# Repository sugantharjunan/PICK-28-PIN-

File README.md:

# PIC 28-Pin Development Board – KiCad PCB Design

A compact and versatile **PIC 28-Pin Development Board** designed using **KiCad EDA** for schematic capture and PCB layout. This project is based on the **PIC16F873A / PIC16F876A / PIC16F877A family architecture**, providing GPIO breakout pins, push buttons, EEPROM interface, IR sensor support, LEDs, and expansion headers for embedded systems development.

The board is suitable for learning PIC microcontrollers, embedded programming, sensor interfacing, and electronics prototyping.

---

# Project Overview

This project demonstrates:

* PIC 28-pin microcontroller minimum system design
* PCB layout using KiCad
* EEPROM interfacing
* IR sensor interface
* Push-button inputs
* LED status indicators
* GPIO breakout headers
* 3D PCB visualization

---

# Features

* Supports 28-pin PIC microcontroller
* GPIO breakout headers
* Push-button interface
* External EEPROM support
* IR sensor module interface
* Status LEDs
* Compact PCB layout
* Through-hole component design
* Designed using KiCad

---

# Software Used

* KiCad

Official Website: [KiCad Official Website](https://www.kicad.org?utm_source=chatgpt.com)

---

# Hardware Components

| Component               | Description                  |
| ----------------------- | ---------------------------- |
| PIC16F873A / PIC16F876A | PIC Microcontroller          |
| AT24Cxx                 | EEPROM Memory IC             |
| TSOP1738                | IR Receiver Module           |
| Push Buttons            | User Input                   |
| LEDs                    | Status Indicators            |
| Capacitors              | Power filtering              |
| Resistors               | Pull-up and current limiting |
| Pin Headers             | GPIO breakout                |

---

# Project Structure

```bash id="f4jv7a"
PIC-28PIN-DEVELOPMENT-BOARD/
│
├── Schematic/
│   └── pic_28pin_board.kicad_sch
│
├── PCB/
│   └── pic_28pin_board.kicad_pcb
│
├── Gerber/
│   └── Manufacturing_Files
│
├── Images/
│   ├── PIC_28PIN_3D_FRONT.png
│   ├── PIC_28PIN_3D_BACK.png
│   ├── PIC_28PIN_PCB.png
│   └── PIC_28PIN_SCHEMATIC.png
│
└── README.md
```

---

# Circuit Description

The development board is centered around a **28-pin PIC microcontroller** with additional peripheral support circuits.

The design includes:

* Push-button input interface
* EEPROM communication support
* IR receiver module connection
* LED output indicators
* GPIO expansion headers
* Power regulation and filtering

---

# Working Principle

1. +5V supply powers the microcontroller and peripherals.
2. PIC microcontroller executes embedded firmware.
3. Push buttons provide user input.
4. EEPROM stores external data.
5. IR receiver detects remote control signals.
6. LEDs indicate system status or outputs.
7. GPIO headers allow external module interfacing.

---

# PCB Design

The PCB was designed with:

* Organized GPIO routing
* Compact component placement
* Easy soldering access
* Through-hole assembly
* Proper grounding layout
* Beginner-friendly prototyping structure

---

# Electrical Specifications

| Parameter         | Value             |
| ----------------- | ----------------- |
| Microcontroller   | PIC 28-Pin Series |
| Supply Voltage    | +5V DC            |
| EEPROM Support    | Yes               |
| IR Sensor Support | Yes               |
| GPIO Expansion    | Yes               |
| PCB Tool          | KiCad             |

---

# Pin Interfaces

The board exposes:

* Digital GPIO Pins
* Analog Input Pins
* UART Communication
* I2C Interface
* SPI Interface
* EEPROM Interface
* IR Sensor Interface

for embedded application development.

---

# Applications

* Embedded Systems Development
* PIC Programming Practice
* Sensor Interfacing
* IR Remote Projects
* EEPROM Data Logging
* Robotics
* Automation Projects
* Academic Embedded Labs

---

# Development Notes

Compatible with:

* MPLAB X IDE
* XC8 Compiler
* PICkit Programmer
* MikroC
* Embedded C Programming

---

# Future Improvements

* Add onboard USB programmer
* Add voltage regulator section
* Add LCD display connector
* Add relay driver outputs
* Add wireless communication modules

---

This project is open-source and available under the MIT License.

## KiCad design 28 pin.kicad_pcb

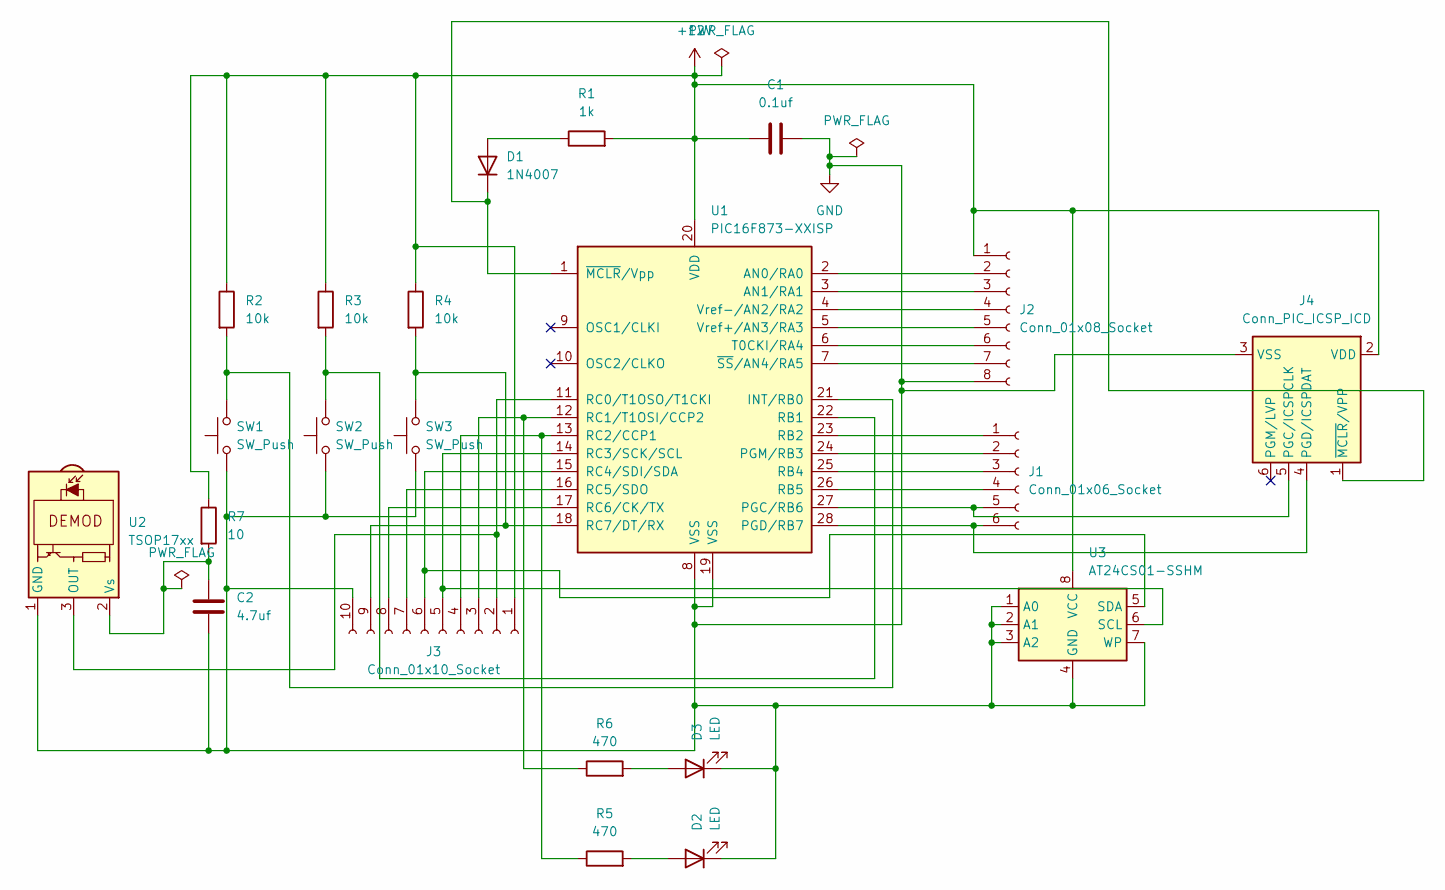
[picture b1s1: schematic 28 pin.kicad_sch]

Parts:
C1: 0.1uf; CP_Radial_D4.0mm_P1.50mm
C2: 4.7uf; CP_Radial_D4.0mm_P1.50mm
D1: 1N4007; D_DO-41_SOD81_P10.16mm_Horizontal
D2, D3: LED; LED_D3.0mm
J1: Conn_01x06_Socket; PinSocket_1x06_P1.27mm_Vertical
J2: Conn_01x08_Socket; PinSocket_1x08_P1.27mm_Vertical
J3: Conn_01x10_Socket; PinSocket_1x10_P1.27mm_Vertical
J4: Conn_PIC_ICSP_ICD; PinSocket_1x06_P2.54mm_Horizontal
R1: 1k; R_Axial_DIN0204_L3.6mm_D1.6mm_P7.62mm_Horizontal
R2, R3, R4: 10k; R_Axial_DIN0204_L3.6mm_D1.6mm_P7.62mm_Horizontal
R5, R6: 470; R_Axial_DIN0204_L3.6mm_D1.6mm_P7.62mm_Horizontal
R7: 10; R_Axial_DIN0204_L3.6mm_D1.6mm_P7.62mm_Horizontal
SW1, SW2, SW3: SW_Push; SW_PUSH_6mm_H5mm
U1: PIC16F873-XXISP; DIP-28_W7.62mm
U2: TSOP17xx; Vishay_CAST-3Pin
U3: AT24CS01-SSHM; SOIC-8_3.9x4.9mm_P1.27mm

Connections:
+12V: C1.1, J2.1, J3.1, J4.2 (VDD), R1.2, R2.1, R3.1, R4.1, R7.1, U1.20 (VDD), U3.8 (VCC)
GND: C1.2, C2.2, D2.1 (K), D3.1 (K), J2.8, J3.10, J4.3 (VSS), SW1.1, SW2.1, SW3.1, U1.8 (VSS), U1.19 (VSS), U2.1 (GND), U3.1 (A0), U3.2 (A1), U3.3 (A2), U3.4 (GND), U3.7 (WP)
unnamed: D1.2 (A), R1.1
unnamed: D1.1 (K), J4.1 (~MCLR/VPP), U1.1 (~MCLR/Vpp)
unnamed: D2.2 (A), R5.2
unnamed: D3.2 (A), R6.2
unnamed: J1.1, U1.23 (RB2)
unnamed: J1.2, U1.24 (PGM/RB3)
unnamed: J1.3, U1.25 (RB4)
unnamed: J1.4, U1.26 (RB5)
unnamed: J1.5, J4.5 (PGC/ICSPCLK), U1.27 (PGC/RB6)
unnamed: J1.6, J4.4 (PGD/ICSPDAT), U1.28 (PGD/RB7)
unnamed: J2.2, U1.2 (AN0/RA0)
unnamed: J2.3, U1.3 (AN1/RA1)
unnamed: J2.4, U1.4 (Vref-/AN2/RA2)
unnamed: J2.5, U1.5 (Vref+/AN3/RA3)
unnamed: J2.6, U1.6 (T0CKI/RA4)
unnamed: J2.7, U1.7 (~SS/AN4/RA5)
unnamed: J3.2, U1.11 (RC0/T1OSO/T1CKI), U2.3 (OUT)
unnamed: J3.3, R6.1, U1.12 (RC1/T1OSI/CCP2)
unnamed: J3.4, R5.1, U1.13 (RC2/CCP1)
unnamed: J3.5, U1.14 (RC3/SCK/SCL), U3.6 (SCL)
unnamed: J3.6, U1.15 (RC4/SDI/SDA), U3.5 (SDA)
unnamed: J3.7, U1.16 (RC5/SDO)
unnamed: J3.8, U1.17 (RC6/CK/TX)
unnamed: J3.9, R4.2, SW3.2, U1.18 (RC7/DT/RX)
unnamed: R2.2, SW1.2, U1.21 (INT/RB0)
unnamed: R3.2, SW2.2, U1.22 (RB1)
unnamed: C2.1, R7.2, U2.2 (Vs)

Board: 2 copper layers, 22 parts (0 on the bottom side), 29 nets, no tracks yet.
